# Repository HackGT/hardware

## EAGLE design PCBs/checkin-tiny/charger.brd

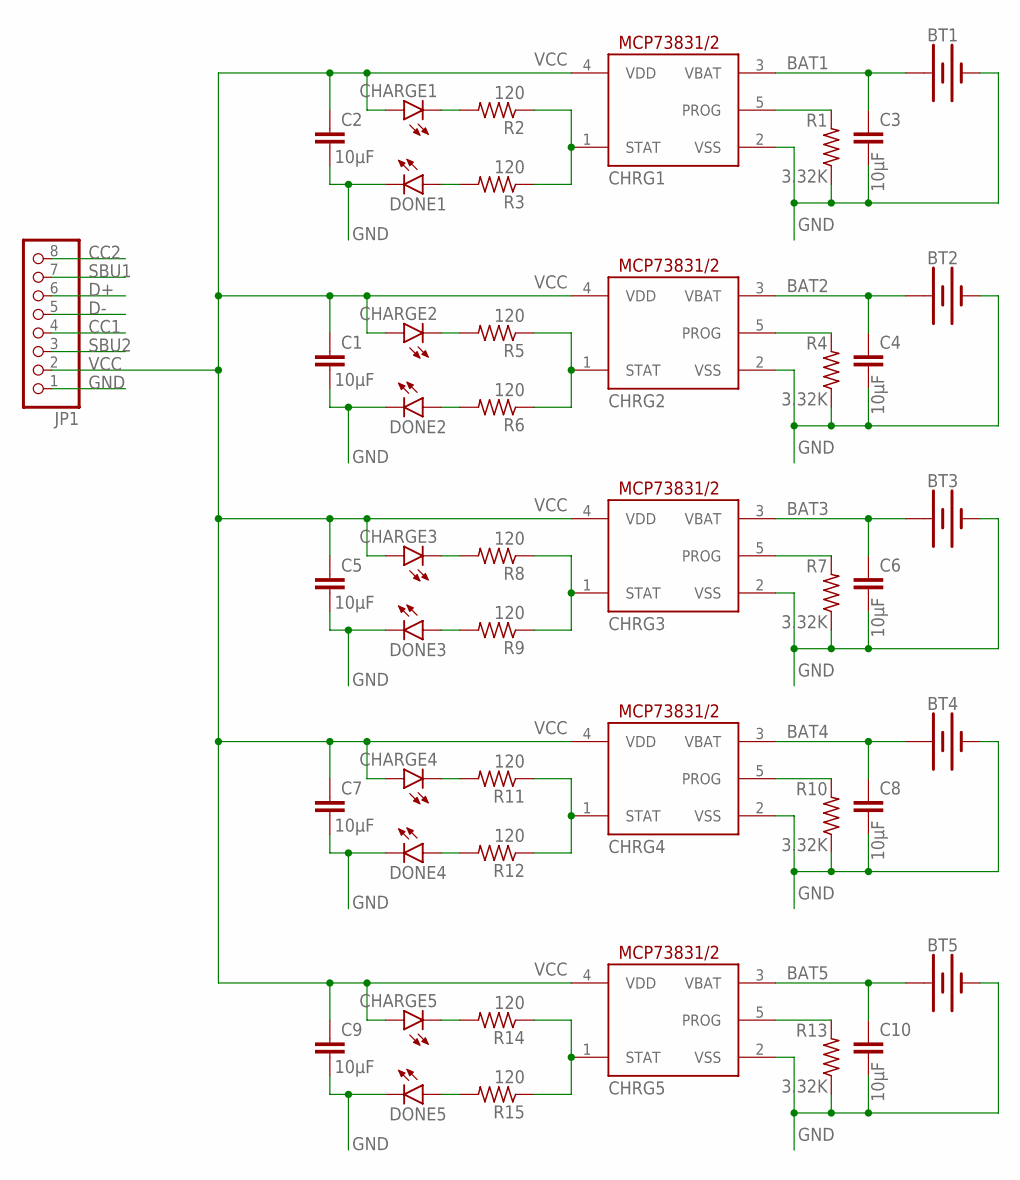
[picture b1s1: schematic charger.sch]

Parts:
BT1, BT2, BT3, BT4, BT5: BATTERY-18650; BATTERY_18650-HOLDER
C1, C2, C3, C4, C5, C6, C7, C8, C9, C10: 10µF; C1206
CHARGE1, CHARGE2, CHARGE3, CHARGE4, CHARGE5: LED3MM
CHRG1, CHRG2, CHRG3, CHRG4, CHRG5: MCP73831/OT; SOT23-5L
DONE1, DONE2, DONE3, DONE4, DONE5: LED3MM
JP1: PINHD-1X8CLEANBIG; 1X08-CLEANBIG
R1, R4, R7, R10, R13: 3.32K; R1206
R2, R3, R5, R6, R8, R9, R11, R12, R14, R15: 120; R1206

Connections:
BAT1: BT1.PWR@1 (+), BT1.PWR@2 (+), BT1.PWR@3 (+), C3.1, CHRG1.3 (VBAT)
BAT2: BT2.PWR@1 (+), BT2.PWR@2 (+), BT2.PWR@3 (+), C4.1, CHRG2.3 (VBAT)
BAT3: BT3.PWR@1 (+), BT3.PWR@2 (+), BT3.PWR@3 (+), C6.1, CHRG3.3 (VBAT)
BAT4: BT4.PWR@1 (+), BT4.PWR@2 (+), BT4.PWR@3 (+), C8.1, CHRG4.3 (VBAT)
BAT5: BT5.PWR@1 (+), BT5.PWR@2 (+), BT5.PWR@3 (+), C10.1, CHRG5.3 (VBAT)
CC1: JP1.4
CC2: JP1.8
D+: JP1.6
D-: JP1.5
GND: BT1.GND@1 (-), BT1.GND@2 (-), BT1.GND@3 (-), BT2.GND@1 (-), BT2.GND@2 (-), BT2.GND@3 (-), BT3.GND@1 (-), BT3.GND@2 (-), BT3.GND@3 (-), BT4.GND@1 (-), BT4.GND@2 (-), BT4.GND@3 (-), BT5.GND@1 (-), BT5.GND@2 (-), BT5.GND@3 (-), C1.2, C2.2, C3.2, C4.2, C5.2, C6.2, C7.2, C8.2, C9.2, C10.2, CHRG1.2 (VSS), CHRG2.2 (VSS), CHRG3.2 (VSS), CHRG4.2 (VSS), CHRG5.2 (VSS), DONE1.K (C), DONE2.K (C), DONE3.K (C), DONE4.K (C), DONE5.K (C), JP1.1, R1.1, R4.1, R7.1, R10.1, R13.1
unnamed: DONE1.A, R3.2
unnamed: CHRG1.1 (STAT), R2.1, R3.1
unnamed: CHARGE2.K (C), R5.2
unnamed: DONE2.A, R6.2
unnamed: CHRG2.1 (STAT), R5.1, R6.1
unnamed: CHRG2.5 (PROG), R4.2
unnamed: CHARGE1.K (C), R2.2
unnamed: CHARGE3.K (C), R8.2
unnamed: DONE3.A, R9.2
unnamed: CHRG1.5 (PROG), R1.2
unnamed: CHRG3.1 (STAT), R8.1, R9.1
unnamed: CHRG3.5 (PROG), R7.2
unnamed: CHARGE4.K (C), R11.2
unnamed: DONE4.A, R12.2
unnamed: CHRG4.1 (STAT), R11.1, R12.1
unnamed: CHRG4.5 (PROG), R10.2
unnamed: CHARGE5.K (C), R14.2
unnamed: DONE5.A, R15.2
unnamed: CHRG5.1 (STAT), R14.1, R15.1
unnamed: CHRG5.5 (PROG), R13.2
SBU1: JP1.7
SBU2: JP1.3
VCC: C1.1, C2.1, C5.1, C7.1, C9.1, CHARGE1.A, CHARGE2.A, CHARGE3.A, CHARGE4.A, CHARGE5.A, CHRG1.4 (VDD), CHRG2.4 (VDD), CHRG3.4 (VDD), CHRG4.4 (VDD), CHRG5.4 (VDD), JP1.2

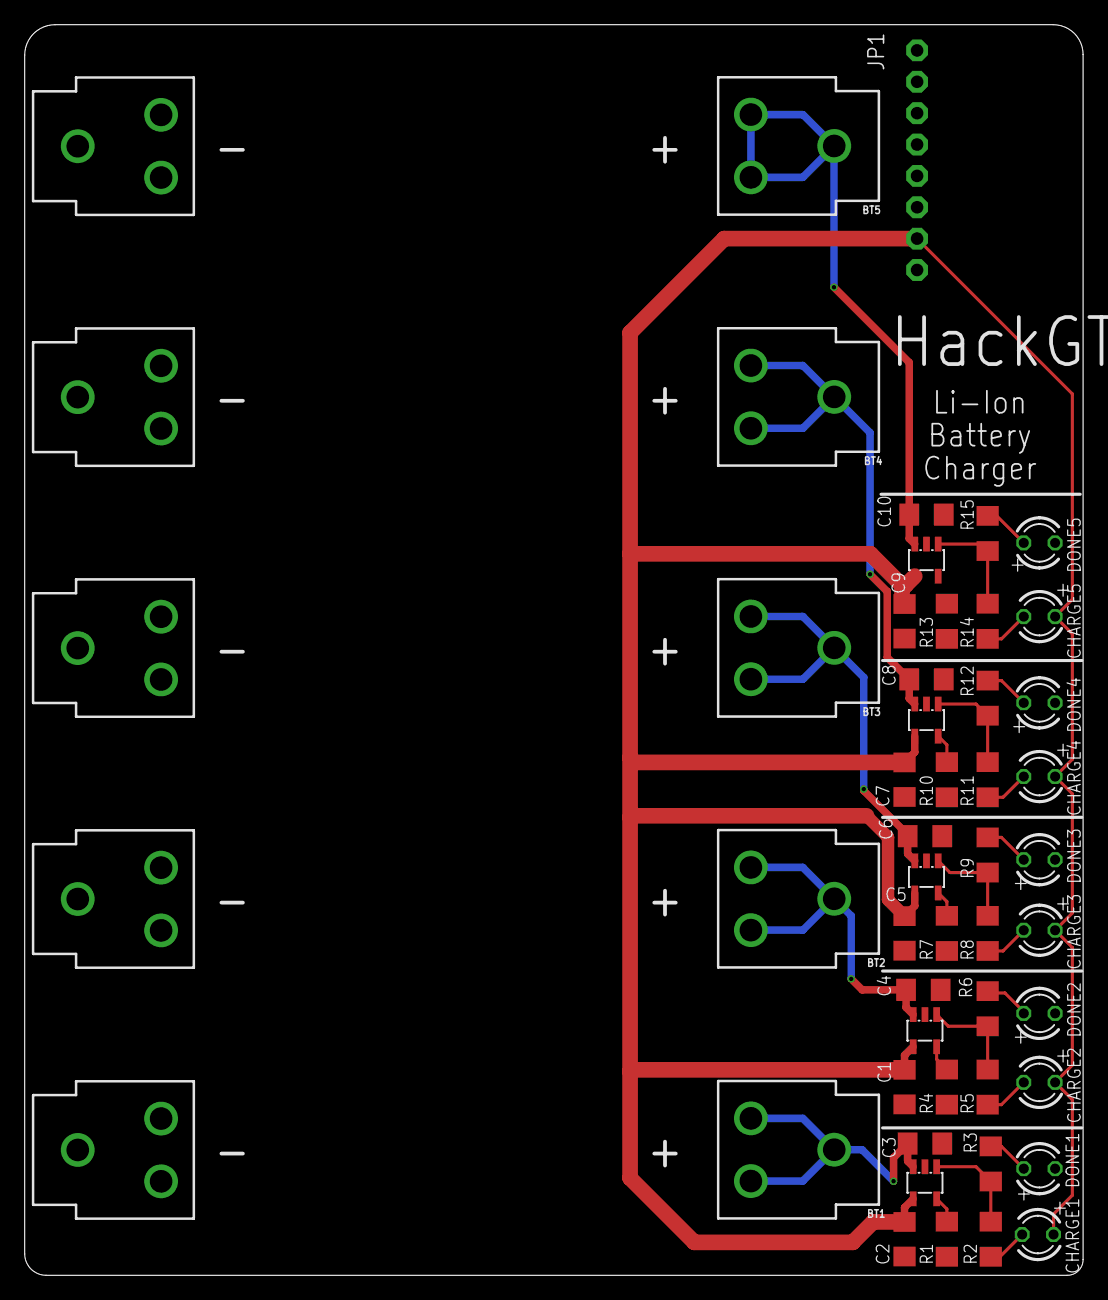
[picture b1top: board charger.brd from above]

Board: 2 copper layers, 85.7 x 101.3 mm, 46 parts (0 on the bottom side), 27 nets.

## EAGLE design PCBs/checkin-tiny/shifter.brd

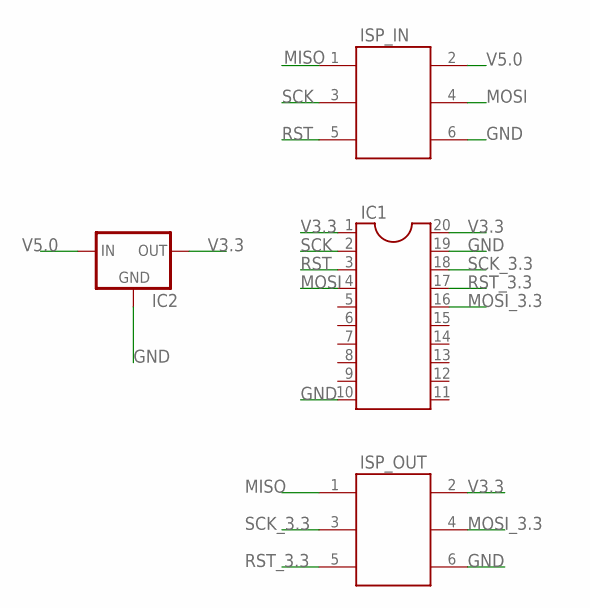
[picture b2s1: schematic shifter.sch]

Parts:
IC1: DIL20
IC2: MCP1700INLINE; TO92-INLINE
ISP_IN: 61200621621
ISP_OUT: 61200621621

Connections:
GND: IC1.10, IC1.19, IC2.1 (GND), ISP_IN.6, ISP_OUT.6
MISO: ISP_IN.1, ISP_OUT.1
MOSI: IC1.4, ISP_IN.4
MOSI_3.3: IC1.16, ISP_OUT.4
RST: IC1.3, ISP_IN.5
RST_3.3: IC1.17, ISP_OUT.5
SCK: IC1.2, ISP_IN.3
SCK_3.3: IC1.18, ISP_OUT.3
V3.3: IC1.1, IC1.20, IC2.3 (OUT), ISP_OUT.2
V5.0: IC2.2 (IN), ISP_IN.2

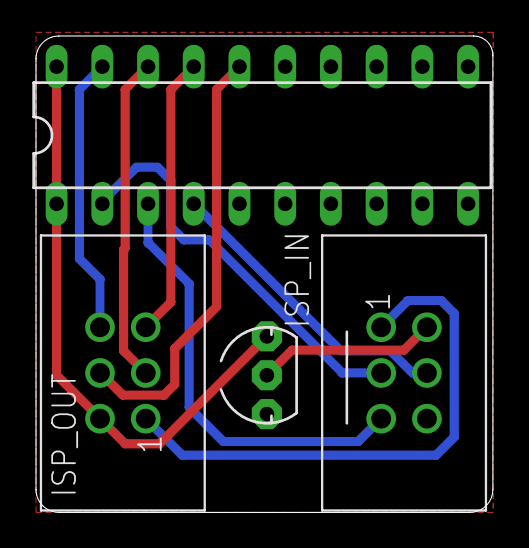
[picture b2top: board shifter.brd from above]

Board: 2 copper layers, 25.4 x 26.5 mm, 4 parts (0 on the bottom side), 10 nets.

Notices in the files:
parts and their libraries:
SparkFun-Batteries: Licensing: Creative Commons ShareAlike 4.0 International - https://creativecommons.org/licenses/by-sa/4.0
Wurth_Elektronik_Electromechanic_Wire_to: Copyright: Würth Elektronik
